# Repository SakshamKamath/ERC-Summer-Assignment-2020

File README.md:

# ERC-Summer-Assignment-2020
I have attempted totally 6 questions namely:
4.2.1.1 , 
4.2.1.2 ,
4.2.1.3 ,
4.2.1.4 ,
4.2.2.1 ,
4.2.3.1 .
I have pasted the links of the public tinkercad files of the simulated Arduino Circuits in a Word Document in the file named 
ERC Summer Assignment 2020 . I have also inserted the files of the schematic and the board of the Eagle file .

I have also attempted one of the question(extra) from 4.3 AUTOMATION AND CONTROL 4.3.1.1 
The file c_traj(1) is the python file of the publisher node. 
erc.bag is the rosbag .
rosgraph is the rqt_graph screenshot.

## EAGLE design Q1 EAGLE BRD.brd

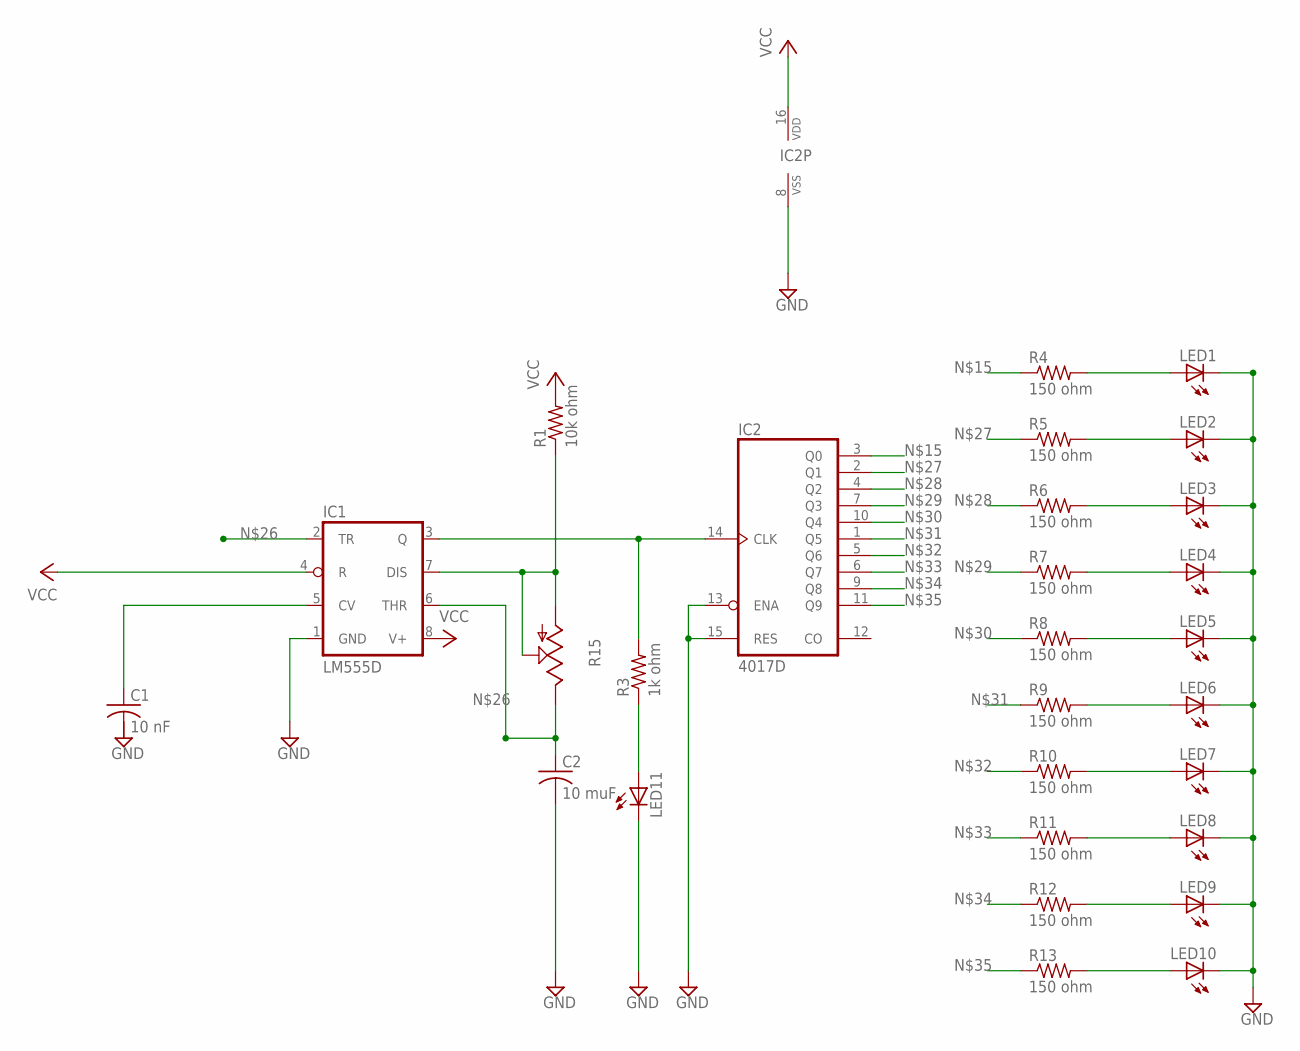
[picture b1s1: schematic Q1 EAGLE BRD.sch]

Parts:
C1: 10 nF; C0805
C2: 10 muF; C0805
IC1: LM555D; SO08
IC2: 4017D; SO16
LED1, LED2, LED3, LED4, LED5, LED6, LED7, LED8, LED9, LED10, LED11: LED5MM
R1: 10k ohm; M1206
R3: 1k ohm; M1206
R4, R5, R6, R7, R8, R9, R10, R11, R12, R13: 150 ohm; M1206
R15: TRIM_US-S63X; S63X

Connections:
GND: C2.2, IC1.1 (GND), IC2.8 (VSS), IC2.13 (ENA), IC2.15 (RES), LED1.K (C), LED2.K (C), LED3.K (C), LED4.K (C), LED5.K (C), LED6.K (C), LED7.K (C), LED8.K (C), LED9.K (C), LED10.K (C), LED11.K (C)
unnamed: C1.1, IC1.5 (CV)
unnamed: LED11.A, R3.1
unnamed: LED1.A, R4.2
unnamed: LED2.A, R5.2
unnamed: LED3.A, R6.2
unnamed: LED4.A, R7.2
unnamed: LED5.A, R8.2
unnamed: LED6.A, R9.2
unnamed: LED7.A, R10.2
unnamed: LED8.A, R11.2
unnamed: LED9.A, R12.2
unnamed: LED10.A, R13.2
unnamed: IC1.7 (DIS), R1.1, R15.A, R15.S
unnamed: IC2.3 (Q0), R4.1
unnamed: IC1.3 (Q), IC2.14 (CLK), R3.2
unnamed: C2.1, IC1.2 (TR), IC1.6 (THR), R15.E
unnamed: IC2.2 (Q1), R5.1
unnamed: IC2.4 (Q2), R6.1
unnamed: IC2.7 (Q3), R7.1
unnamed: IC2.10 (Q4), R8.1
unnamed: IC2.1 (Q5), R9.1
unnamed: IC2.5 (Q6), R10.1
unnamed: IC2.6 (Q7), R11.1
unnamed: IC2.9 (Q8), R12.1
unnamed: IC2.11 (Q9), R13.1
VCC: IC1.4 (R), IC1.8 (V+), IC2.16 (VDD), R1.2

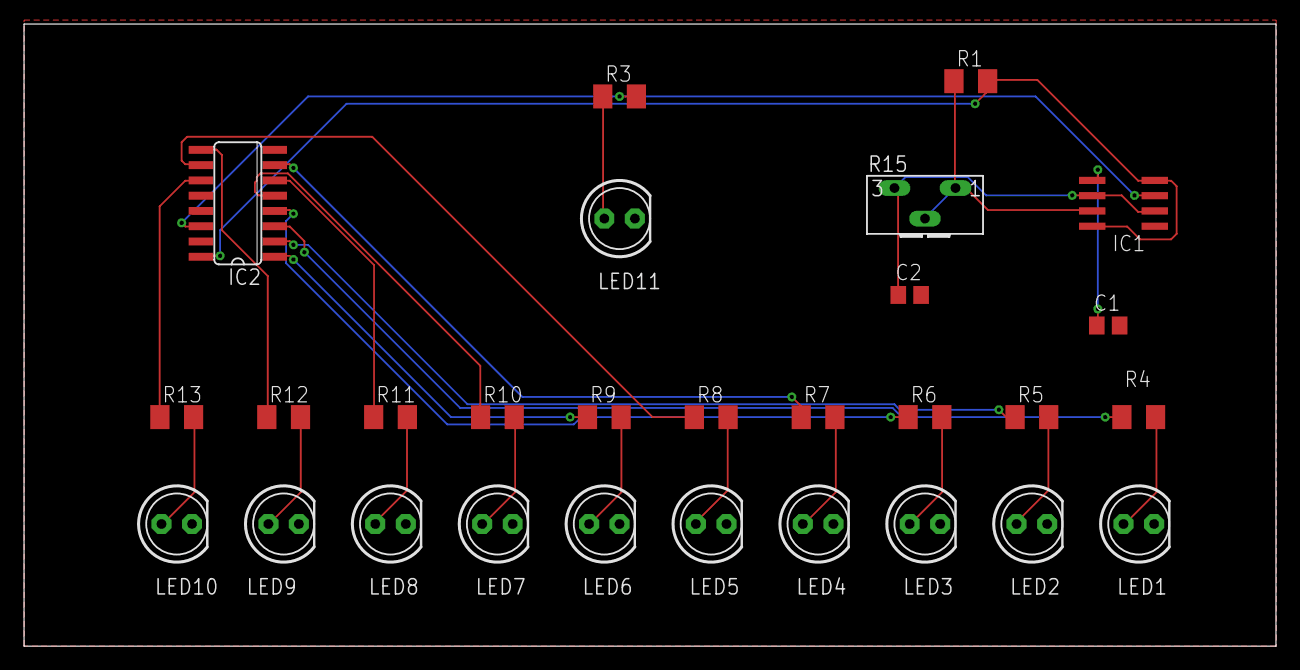
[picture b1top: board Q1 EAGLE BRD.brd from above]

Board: 2 copper layers, 104.1 x 51.7 mm, 28 parts (0 on the bottom side), 27 nets.

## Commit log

2020-06-14 Add files via upload
    c_traj(1).py is the python file for the publisher node which moves the turtebot in a circle in gazebo
